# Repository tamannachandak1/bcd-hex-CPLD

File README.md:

Open: 
CPLD_bcdtohex.kicad_pcb, CPLD_bcdtohex.kicad_sch

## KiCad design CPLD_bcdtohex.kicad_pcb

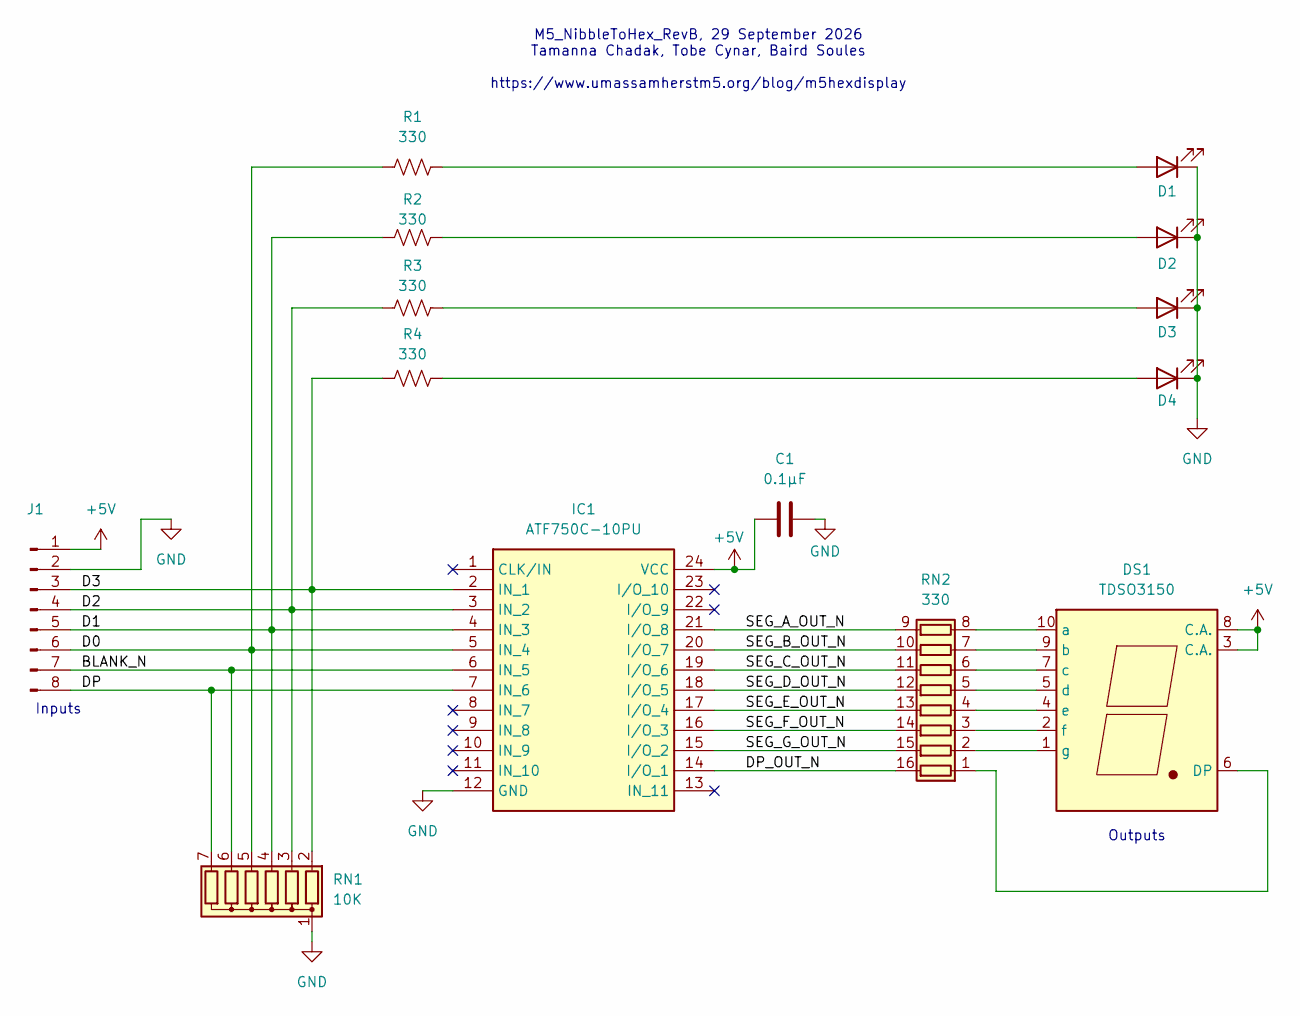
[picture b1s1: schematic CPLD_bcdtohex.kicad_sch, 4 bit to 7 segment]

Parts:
C1: 0.1µF; C_Disc_D5.0mm_W2.5mm_P2.50mm
D1, D2, D3, D4: LED; LED_D3.0mm
DS1: TDSO3150; DIP-10_W7.62mm
IC1: ATF750C-10PU; DIP-24_W7.62mm; Mouser Part Number 556-AF750C10PU
J1: Conn_01x08_Pin; PinHeader_1x08_P2.54mm_Vertical
R1, R2, R3, R4: 330; R_Axial_DIN0207_L6.3mm_D2.5mm_P7.62mm_Horizontal
RN1: 10K; R_Array_SIP7
RN2: 330; DIP-16_W7.62mm

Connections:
+5V: C1.1, DS1.3 (C.A.), DS1.8 (C.A.), IC1.24 (VCC), J1.1
/BLANK_N: IC1.6 (IN_5), J1.7, RN1.6 (R5)
/D0: IC1.5 (IN_4), J1.6, R1.1, RN1.5 (R4)
/D1: IC1.4 (IN_3), J1.5, R2.1, RN1.4 (R3)
/D2: IC1.3 (IN_2), J1.4, R3.1, RN1.3 (R2)
/D3: IC1.2 (IN_1), J1.3, R4.1, RN1.2 (R1)
/DP: IC1.7 (IN_6), J1.8, RN1.7 (R6)
/DP_OUT_N: IC1.14 (I/O_1), RN2.16 (R1.2)
/SEG_A_OUT_N: IC1.21 (I/O_8), RN2.9 (R8.2)
/SEG_B_OUT_N: IC1.20 (I/O_7), RN2.10 (R7.2)
/SEG_C_OUT_N: IC1.19 (I/O_6), RN2.11 (R6.2)
/SEG_D_OUT_N: IC1.18 (I/O_5), RN2.12 (R5.2)
/SEG_E_OUT_N: IC1.17 (I/O_4), RN2.13 (R4.2)
/SEG_F_OUT_N: IC1.16 (I/O_3), RN2.14 (R3.2)
/SEG_G_OUT_N: IC1.15 (I/O_2), RN2.15 (R2.2)
GND: C1.2, D1.1 (K), D2.1 (K), D3.1 (K), D4.1 (K), IC1.12 (GND), J1.2, RN1.1 (common)
unnamed: D1.2 (A), R1.2
unnamed: D2.2 (A), R2.2
unnamed: D3.2 (A), R3.2
unnamed: D4.2 (A), R4.2
unnamed: DS1.6 (DP), RN2.1 (R1.1)
unnamed: DS1.10 (a), RN2.8 (R8.1)
unnamed: DS1.9 (b), RN2.7 (R7.1)
unnamed: DS1.7 (c), RN2.6 (R6.1)
unnamed: DS1.5 (d), RN2.5 (R5.1)
unnamed: DS1.4 (e), RN2.4 (R4.1)
unnamed: DS1.2 (f), RN2.3 (R3.1)
unnamed: DS1.1 (g), RN2.2 (R2.1)

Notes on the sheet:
Outputs
M5_NibbleToHex_RevB, 29 September 2026 Tamanna Chadak, Tobe Cynar, Baird Soules https://www.umassamherstm5.org/blog/m5hexdisplay
Inputs

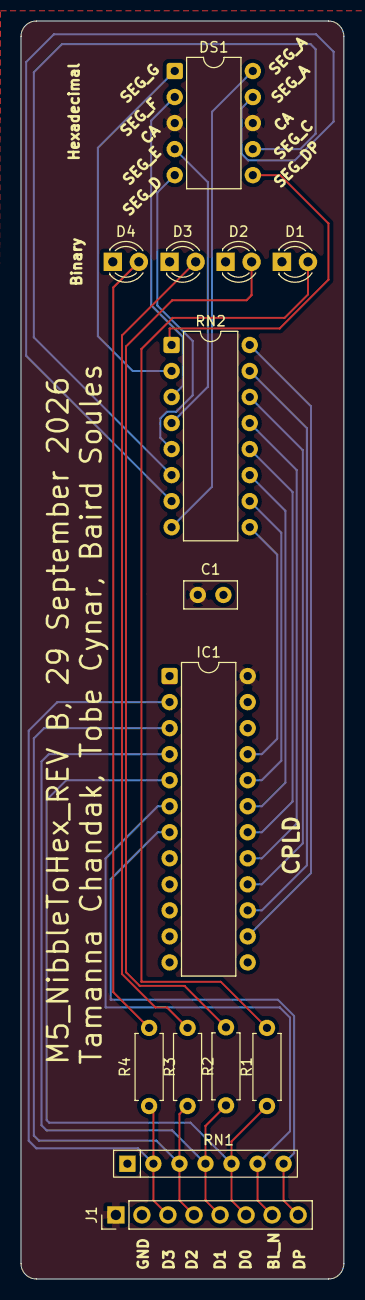
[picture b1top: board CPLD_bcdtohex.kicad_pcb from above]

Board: 4 copper layers, 31.5 x 122.8 mm, 14 parts (0 on the bottom side), 28 nets.
